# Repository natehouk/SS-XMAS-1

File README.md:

View this project on [CADLAB.io](https://cadlab.io/project/28703).

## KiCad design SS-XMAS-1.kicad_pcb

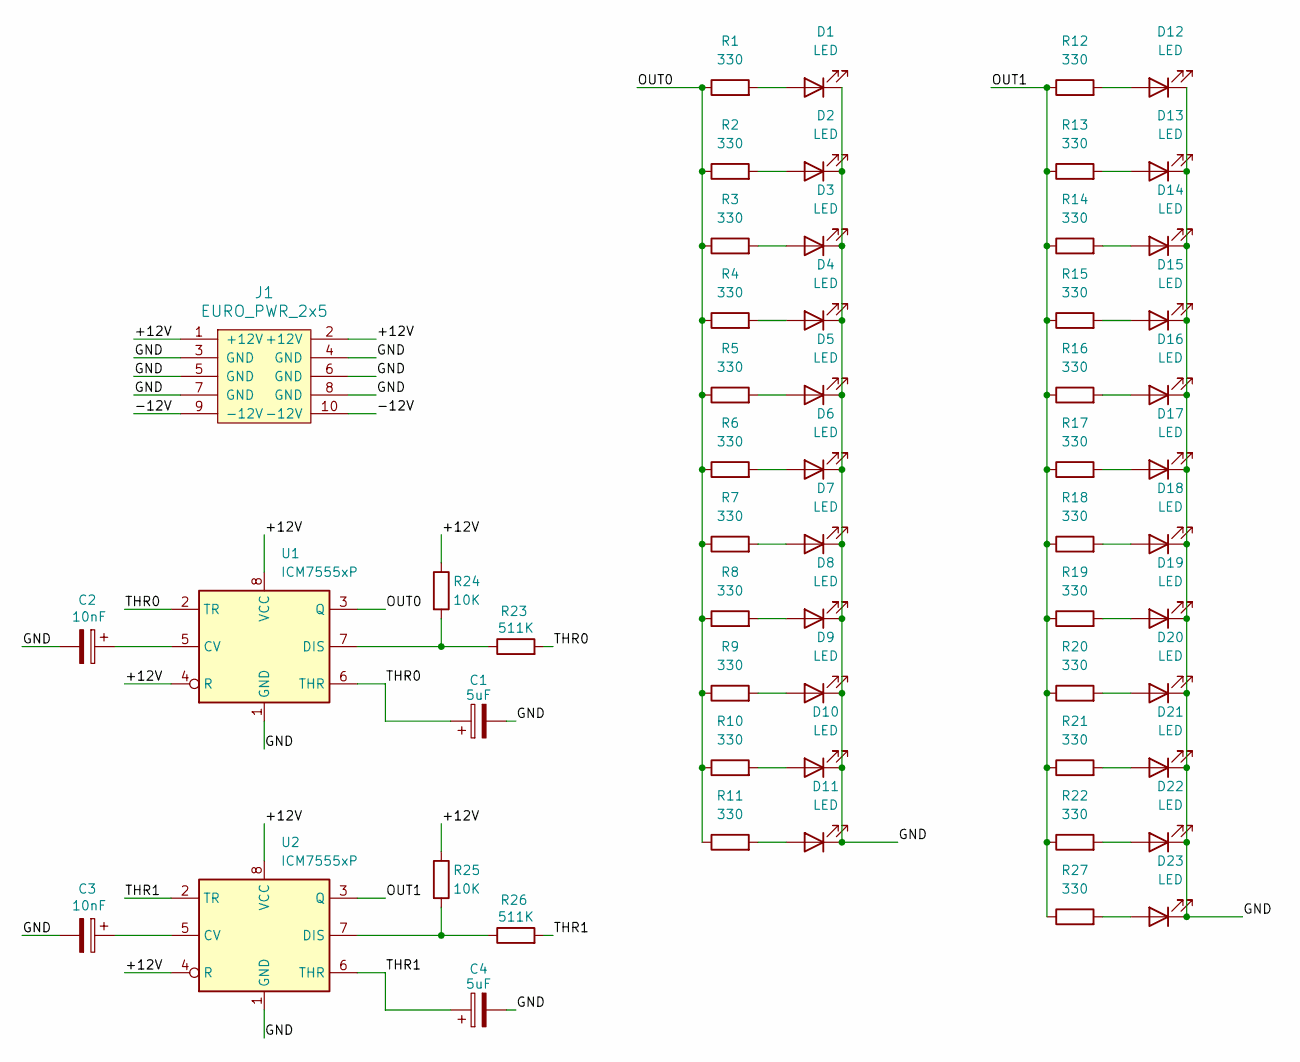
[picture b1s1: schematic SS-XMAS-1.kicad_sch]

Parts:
C1, C4: 5uF; CP_Radial_D5.0mm_P2.50mm
C2, C3: 10nF; CP_Radial_D5.0mm_P2.50mm
D1, D2, D3, D4, D5, D6, D7, D8, D9, D10, D11: LED; LED_D5.0mm
D12, D13, D14, D15, D16, D17, D18, D19, D20, D21, D22, D23: LED; LED_D3.0mm
J1: EURO_PWR_2x5; PinHeader_2x05_P2.54mm_Vertical
R1, R2, R3, R4, R5, R6, R7, R8, R9, R10, R11, R12, R13, R14, R15, R16, R17, R18, R19, R20, R21, R22, R27: 330; R_Axial_DIN0207_L6.3mm_D2.5mm_P10.16mm_Horizontal
R23, R26: 511K; R_Axial_DIN0207_L6.3mm_D2.5mm_P10.16mm_Horizontal
R24, R25: 10K; R_Axial_DIN0207_L6.3mm_D2.5mm_P10.16mm_Horizontal
U1, U2: ICM7555xP; DIP-8_W7.62mm

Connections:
/+12V: J1.1 (+12V), J1.2 (+12V), R24.1, R25.1, U1.4 (R), U1.8 (VCC), U2.4 (R), U2.8 (VCC)
/-12V: J1.9 (-12V), J1.10 (-12V)
/GND: C1.2, C2.2, C3.2, C4.2, D1.1 (K), D2.1 (K), D3.1 (K), D4.1 (K), D5.1 (K), D6.1 (K), D7.1 (K), D8.1 (K), D9.1 (K), D10.1 (K), D11.1 (K), D12.1 (K), D13.1 (K), D14.1 (K), D15.1 (K), D16.1 (K), D17.1 (K), D18.1 (K), D19.1 (K), D20.1 (K), D21.1 (K), D22.1 (K), D23.1 (K), J1.3 (GND), J1.4 (GND), J1.5 (GND), J1.6 (GND), J1.7 (GND), J1.8 (GND), U1.1 (GND), U2.1 (GND)
/OUT0: R1.1, R2.1, R3.1, R4.1, R5.1, R6.1, R7.1, R8.1, R9.1, R10.1, R11.1, U1.3 (Q)
/OUT1: R12.1, R13.1, R14.1, R15.1, R16.1, R17.1, R18.1, R19.1, R20.1, R21.1, R22.1, R27.1, U2.3 (Q); also elsewhere on the board
/THR0: C1.1, R23.2, U1.2 (TR), U1.6 (THR)
/THR1: C4.1, R26.2, U2.2 (TR), U2.6 (THR)
unnamed: D1.2 (A), R1.2
unnamed: D2.2 (A), R2.2
unnamed: D3.2 (A), R3.2
unnamed: D4.2 (A), R4.2
unnamed: D5.2 (A), R5.2
unnamed: D6.2 (A), R6.2
unnamed: D7.2 (A), R7.2
unnamed: D8.2 (A), R8.2
unnamed: D9.2 (A), R9.2
unnamed: D10.2 (A), R10.2
unnamed: D11.2 (A), R11.2
unnamed: D12.2 (A), R12.2
unnamed: D13.2 (A), R13.2
unnamed: D14.2 (A), R14.2
unnamed: D15.2 (A), R15.2
unnamed: D16.2 (A), R16.2
unnamed 23: D17.2 (A), R17.2; also elsewhere on the board
unnamed: D18.2 (A), R18.2
unnamed: D19.2 (A), R19.2
unnamed: D20.2 (A), R20.2
unnamed: D21.2 (A), R21.2
unnamed: D22.2 (A), R22.2
unnamed: D23.2 (A), R27.2
unnamed: C2.1, U1.5 (CV)
unnamed: R23.1, R24.2, U1.7 (DIS)
unnamed: C3.1, U2.5 (CV)
unnamed: R25.2, R26.1, U2.7 (DIS)

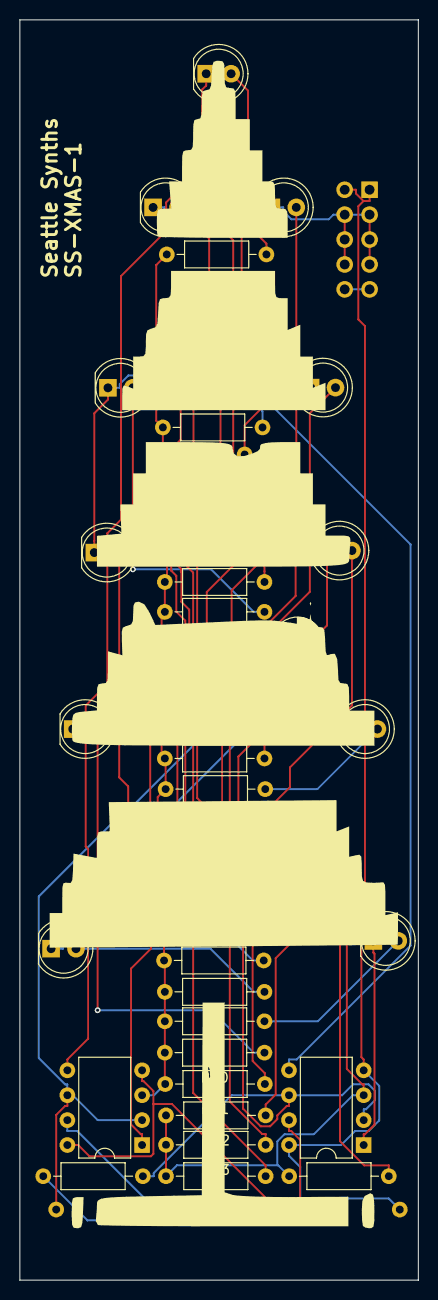
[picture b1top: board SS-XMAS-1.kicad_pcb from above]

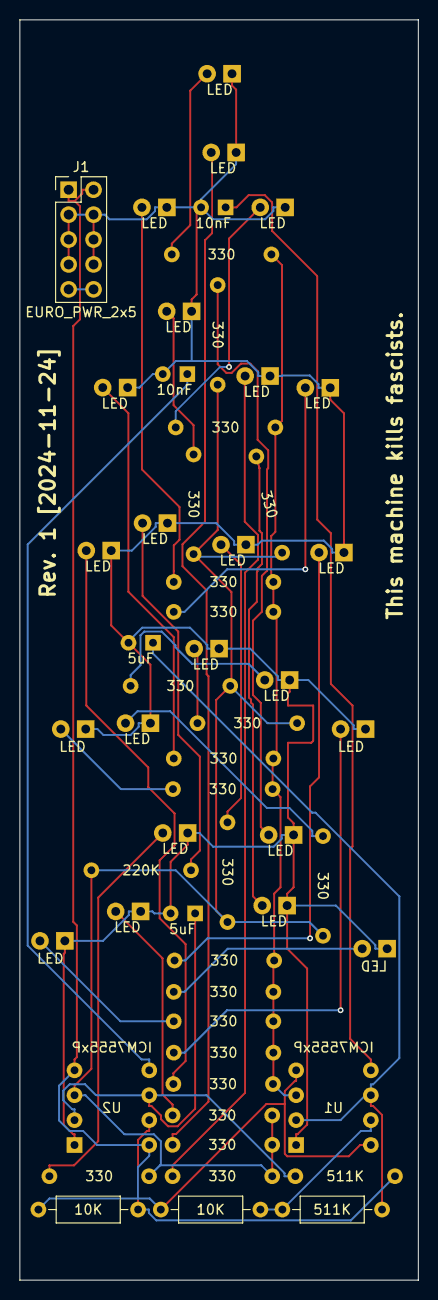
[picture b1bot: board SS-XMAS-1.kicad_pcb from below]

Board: 2 copper layers, 40.6 x 128.5 mm, 61 parts (4 on the bottom side), 34 nets.

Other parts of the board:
BOTTOM_LEFT_MOUNT: MountingHole_3.2mm_M3_Oval
BOTTOM_RIGHT_MOUNT: MountingHole_3.2mm_M3_Oval
R330: 220K; R_Axial_DIN0207_L6.3mm_D2.5mm_P10.16mm_Horizontal
TOP_LEFT_MOUNT: MountingHole_3.2mm_M3_Oval
TOP_RIGHT_MOUNT: MountingHole_3.2mm_M3_Oval

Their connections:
/OUT1: R330.1; also elsewhere on the board
unnamed 23: R330.2; also elsewhere on the board

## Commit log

2024-11-25 Refactor
2024-12-01 Backlink to CADLAB.io has been added.
